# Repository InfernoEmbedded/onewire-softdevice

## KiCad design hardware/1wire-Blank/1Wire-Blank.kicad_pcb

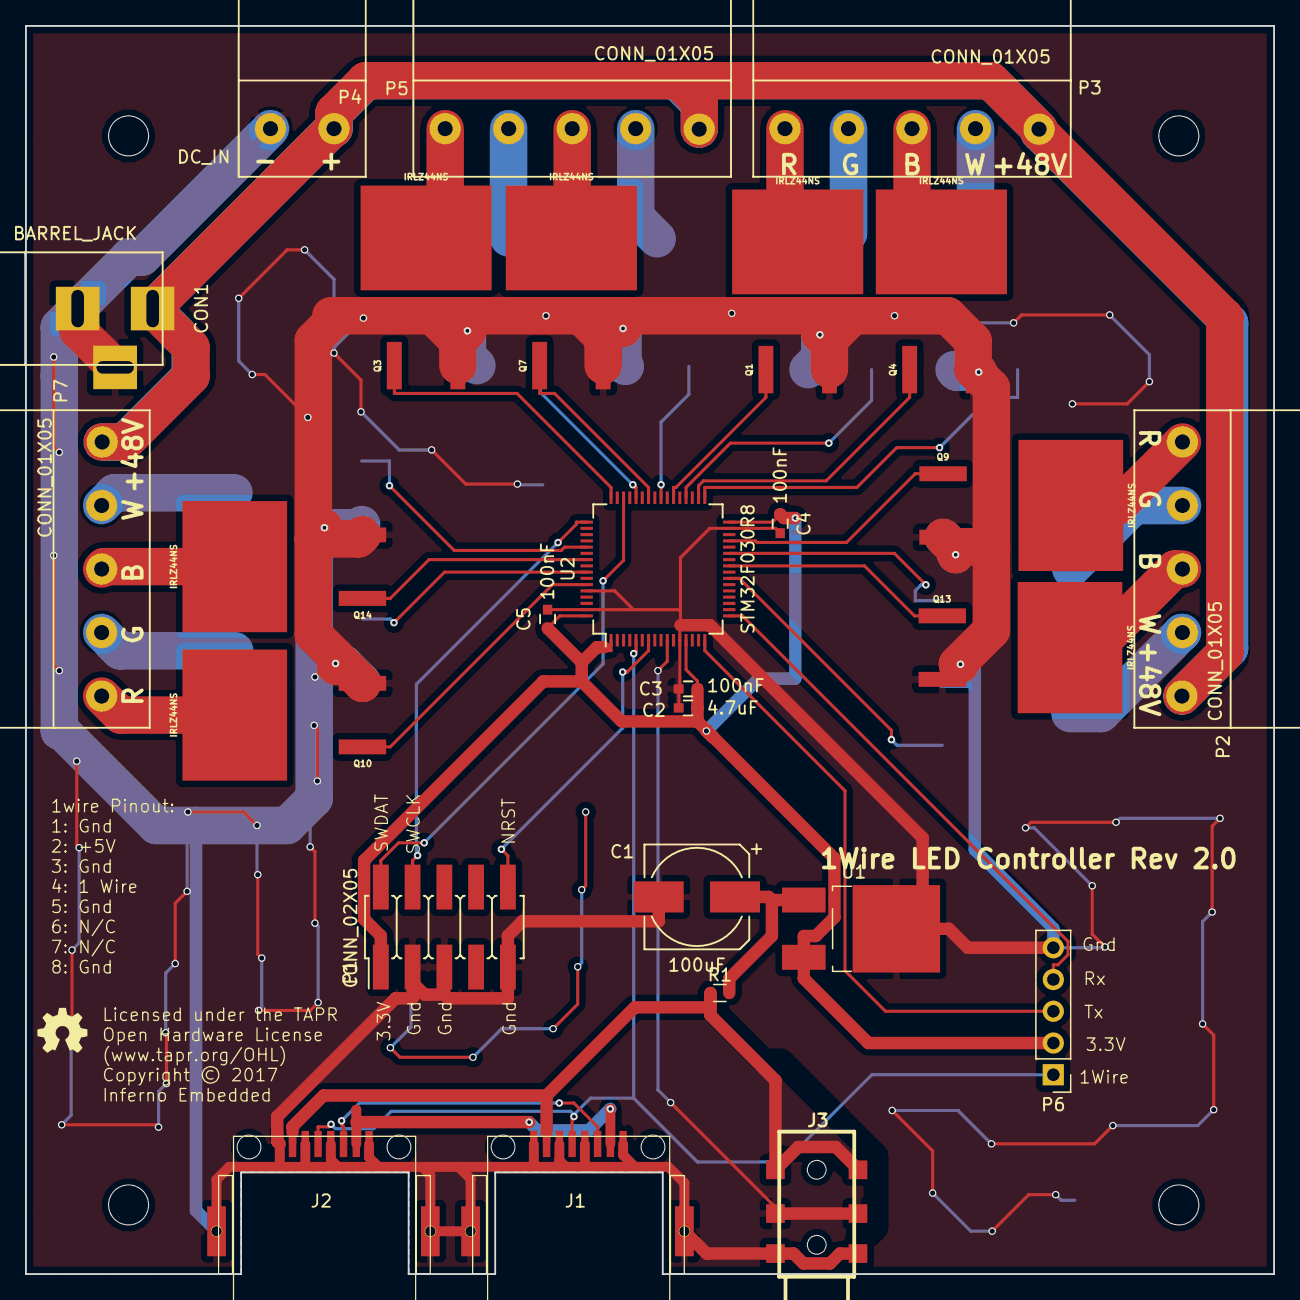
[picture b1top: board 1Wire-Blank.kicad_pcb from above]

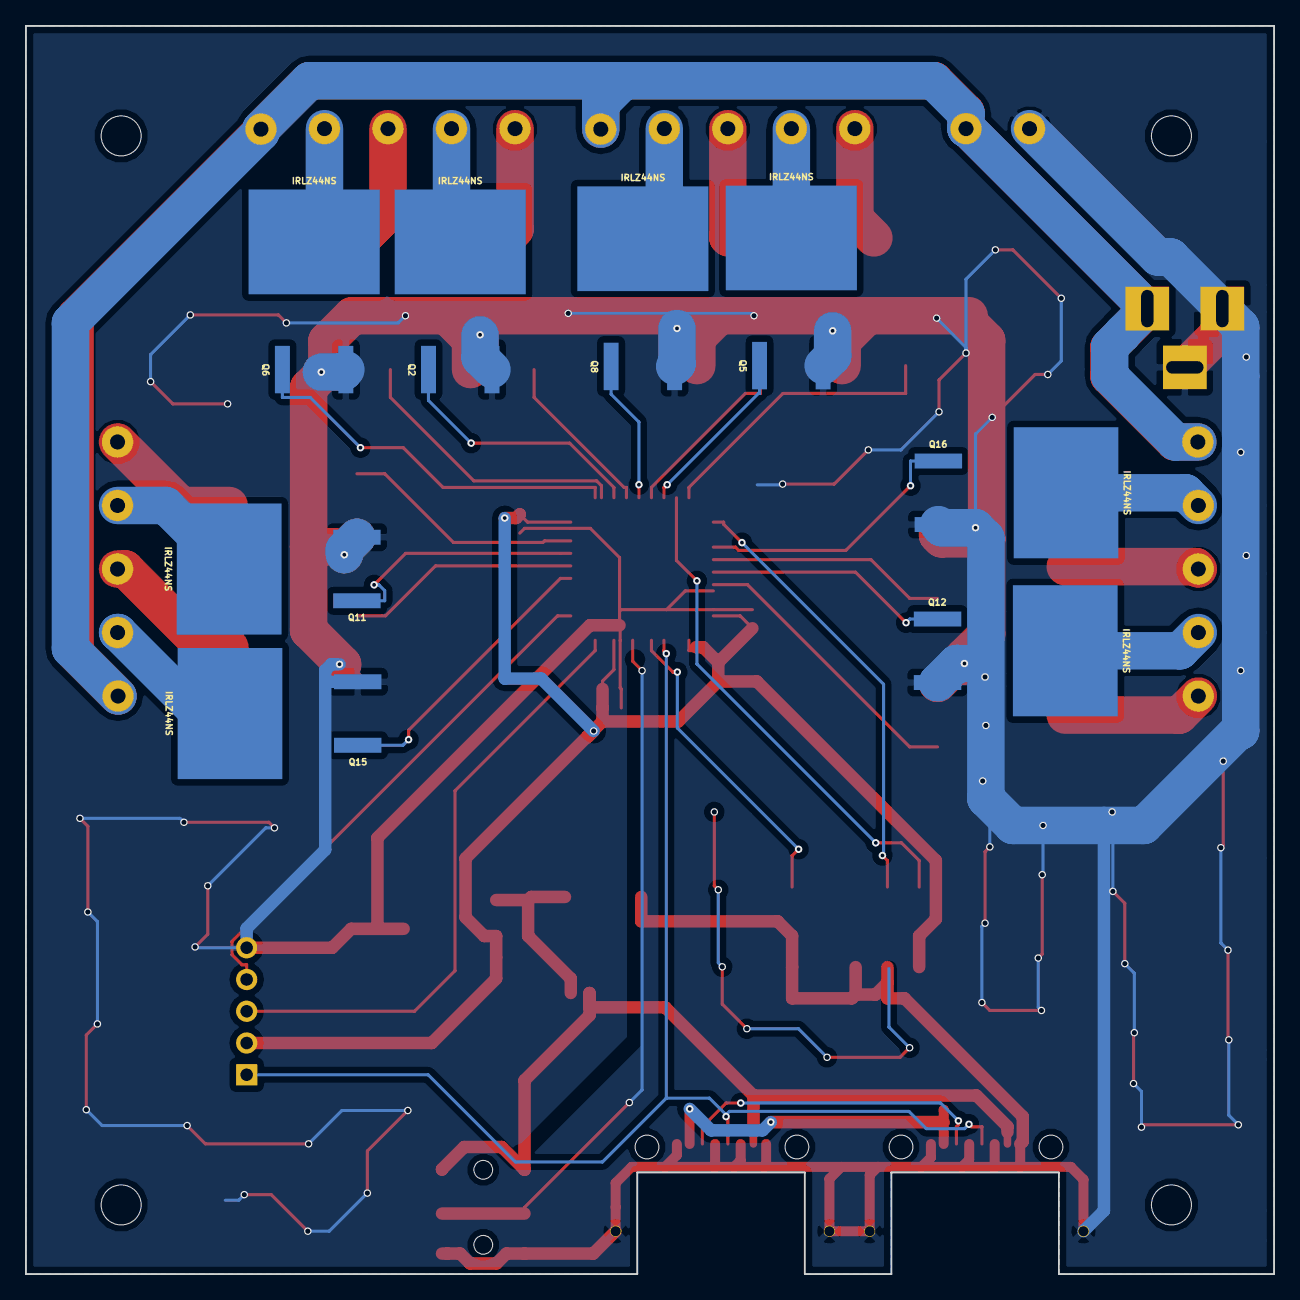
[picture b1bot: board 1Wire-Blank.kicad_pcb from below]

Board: 2 copper layers, 99.8 x 99.8 mm, 39 parts (8 on the bottom side), 46 nets.

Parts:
C1: 100uF; c_elec_8x6.7
C2: 4.7uF; C_0603
C3, C4, C5: 100nF; C_0603
CON1: BARREL_JACK
J1, J2: RJ45; RJ45-ChinaSMD
J3: JACK_STEREO; jack_3.5_pj313d-smt
P1: CONN_02X05; Pin_Header_Straight_SMT_02x05
P2, P3, P5, P7: CONN_01X05; 2EDCK-5.08-5PIN
P4: DC_IN; 2EDCK-5.08-2PIN
P6: CONN_01X05; Pin_Header_Straight_1x05_Pitch2.54mm
Q1, Q2, Q3, Q4, Q5, Q6, Q7, Q8, Q9, Q10, Q11, Q12, Q13, Q14, Q15, Q16: IRLZ44NS; D2PAK
R1: 33R; R_0603
REF1, REF2, REF3, REF4: MountingHole_3.2mm_M3
U1: LP2950; TO-252-2Lead
U2: STM32F030R8; LQFP-64_10x10mm_Pitch0.5mm

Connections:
+3V3: C2.1, C3.1, C4.1, C5.1, P1.1, P6.2, U1.3, U2.1, U2.13, U2.32, U2.64
+5V: J1.2, J2.2, J3.1, R1.1
+48V: CON1.1, P2.5, P3.5, P4.2, P5.5, P7.5
/1W-DATA: J1.4, J2.4, P6.1, U2.5
/CHAN0_B: Q14.1, U2.55
/CHAN0_G: Q12.1, U2.57
/CHAN0_R: Q10.1, U2.59
/CHAN0_W: Q16.1, U2.53
/CHAN1_B: Q7.1, U2.42
/CHAN1_G: Q5.1, U2.44
/CHAN1_R: Q3.1, U2.48
/CHAN1_W: Q8.1, U2.40
/CHAN2_B: Q4.1, U2.34
/CHAN2_G: Q2.1, U2.36
/CHAN2_R: Q1.1, U2.38
/CHAN2_W: Q6.1, U2.33
/CHAN3_B: Q13.1, U2.25
/CHAN3_G: Q11.1, U2.27
/CHAN3_R: Q9.1, U2.29
/CHAN3_W: Q15.1, U2.23
/MAINS_ENABLE: J3.2, U2.10
/SWCLK: P1.4, U2.49
/SWDAT: P1.2, U2.46
/UART_RX: P6.4, U2.17
/UART_TX: P6.3, U2.16
GND: C1.2, C2.2, C3.2, C4.2, C5.2, CON1.2, CON1.3, J1.1, J1.3, J1.5, J1.8, J1.9, J2.1, J2.3, J2.5, J2.8, J2.9, J3.3, P1.3, P1.5, P1.9, P4.1, P6.5, Q1.3, Q2.3, Q3.3, Q4.3, Q5.3, Q6.3, Q7.3, Q8.3, Q9.3, Q10.3, Q11.3, Q12.3, Q13.3, Q14.3, Q15.3, Q16.3, U1.2, U2.12, U2.31, U2.60, U2.63
unnamed: C1.1, R1.2, U1.1
unnamed: J1.6, J2.6
unnamed: J1.7, J2.7
unnamed: P1.10, U2.7
unnamed: P2.1, Q9.2
unnamed: P2.2, Q11.2
unnamed: P2.3, Q13.2
unnamed: P2.4, Q15.2
unnamed: P3.1, Q1.2
unnamed: P3.2, Q2.2
unnamed: P3.3, Q4.2
unnamed: P3.4, Q6.2
unnamed: P5.1, Q3.2
unnamed: P5.2, Q5.2
unnamed: P5.3, Q7.2
unnamed: P5.4, Q8.2
unnamed: P7.1, Q10.2
unnamed: P7.2, Q12.2
unnamed: P7.3, Q14.2
unnamed: P7.4, Q16.2

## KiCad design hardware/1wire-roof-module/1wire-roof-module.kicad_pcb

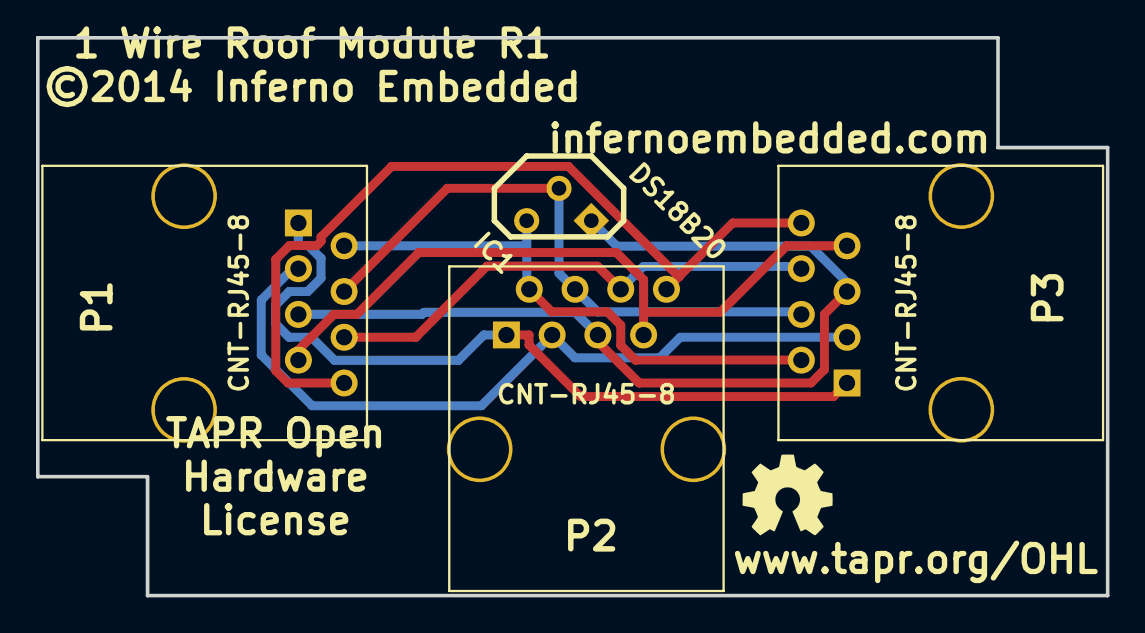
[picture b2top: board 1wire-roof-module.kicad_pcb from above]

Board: 2 copper layers, 59.4 x 31.0 mm, 4 parts (0 on the bottom side), 8 nets.

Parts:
IC1: DS18B20; TO92
P1, P2, P3: CNT-RJ45-8; RJ45_8

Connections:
unnamed: P1.1, P2.1, P3.1
unnamed: P1.8, P2.8, P3.8
unnamed: P1.7, P2.7, P3.7
unnamed: P1.6, P2.6, P3.6
unnamed: IC1.1, P1.5, P2.5, P3.5
unnamed: P1.3, P2.3, P3.3
unnamed: IC1.2, P1.4, P2.4, P3.4
unnamed: IC1.3, P1.2, P2.2, P3.2

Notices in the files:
hardware/1wire-Blank/1Wire-Blank.kicad_pcb:
Licensed under the TAPR Open Hardware License (www.tapr.org/OHL)
Copyright © 2017 Inferno Embedded
hardware/1wire-roof-module/1wire-roof-module.kicad_pcb:
©2014 Inferno Embedded
